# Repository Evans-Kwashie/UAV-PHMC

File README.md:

# UAV-PHMC
### Payload Health & Management Controller

UAV-PHMC is an embedded hardware project: a custom four-layer printed circuit board (PCB) for power management, health monitoring and payload interfacing on a small UAV.

The board is designed to be light and to run from a 2S battery pack. It was modelled around the Ornadyne O1, a crow-shaped, propeller-free flapping-wing reconnaissance drone. This is an independent design and is not affiliated with Ornadyne.

The repository contains the KiCad hardware design files, manufacturing outputs for PCB fabrication and assembly, and an early STM32 firmware foundation with host-side tests.

---

## Project Overview

The UAV-PHMC board is built around the **STM32G071KBUx** microcontroller. It regulates the battery input into the rails the airframe needs, monitors voltage and current, and gives a companion computer and a camera a protected supply and a serial link.

Key design areas include:

- Custom four-layer PCB design.
- STM32G071KBUx microcontroller integration.
- 2S battery input with polyfuse and TVS protection.
- Multi-rail power distribution with two buck regulators.
- Voltage and current monitoring.
- Companion connector and switched camera power connector.
- SWD debug through a Tag-Connect footprint.
- PCB fabrication and assembly preparation.

## Hardware Features

| Feature | Description |
|---|---|
| Microcontroller | STM32G071KBUx |
| PCB | Custom four-layer design |
| Battery input | 2S pack, with polyfuse (F1) and SMAJ10A TVS (D1) |
| Power regulation | Two TPS562202S buck converters |
| Current monitoring | INA226 with a 0.1 ohm shunt |
| Power rails | VBAT_RAW, VBAT_PROT, 5V, 5V_CAM, 3V3 |
| Communication | UART (USART2), I²C (I2C1) |
| Connectors | Battery (J1), companion (J3), camera power (J4) |
| Debug | SWD through Tag-Connect TC2030-NL |
| Design software | KiCad |

## Power Architecture

The hardware design incorporates multiple power domains to support the board and its connected peripherals.

| Power net | Purpose |
|---|---|
| VBAT_RAW | Raw battery input |
| VBAT_PROT | Battery rail after the input protection stage |
| 5V | Main regulated 5V supply |
| 5V_CAM | Camera power supply |
| 3V3 | Logic and microcontroller supply |

The design includes voltage and current monitoring using the INA226, supporting power-system observation and integration.

## Repository Structure

```text
UAV-PHMC/
│
├── hardware/
│   ├── bom/
│   │   └── hardware.csv
│   │
│   ├── gerbers/
│   │   ├── PHMC_gerbers.zip
│   │   ├── hardware-Front.gtl
│   │   ├── hardware-Back.gbl
│   │   ├── hardware-Edge_Cuts.gm1
│   │   └── ... fabrication layers and drill files
│   │
│   ├── libraries/          custom footprints and 3D models
│   ├── pick_place/
│   │   └── hardware-all.pos
│   │
│   ├── hardware.kicad_pro
│   ├── hardware.kicad_sch  top-level schematic
│   ├── Power_Input_Protection.kicad_sch
│   ├── Current_Sense.kicad_sch
│   ├── MCU.kicad_sch
│   ├── Connectors_Comms.kicad_sch
│   ├── hardware.kicad_pcb
│   ├── hardware.net
│   ├── hardware.glb
│   └── front.png, back.png, hardware.png
│
├── firmware/
│   ├── app/              portable application logic
│   ├── board/            board-specific signal definitions
│   ├── drivers/          portable drivers and conversions
│   ├── platform/stm32/   STM32 startup, entry point and linker script
│   ├── tests/            host-native unit tests
│   ├── third_party/      pinned CMSIS files and license notices
│   ├── CMakeLists.txt
│   ├── CMakePresets.json
│   └── README.md         firmware build, test and limitation details
│
├── references/             component datasheets
│   ├── stm32g071c8.pdf
│   ├── tps562202s.pdf
│   └── ina226.pdf
│
├── LICENSE
├── LICENSE-MIT
├── .gitignore
└── README.md
```

## Manufacturing Outputs

The repository includes the following manufacturing-related files:

**Bill of Materials (BOM)**
- `hardware/bom/hardware.csv`

**Gerber and Drill Files**
- `hardware/gerbers/`

**Pick-and-Place Data**
- `hardware/pick_place/hardware-all.pos`

**3D PCB Model**
- `hardware/hardware.glb`

**Gerber Archive**
- `hardware/gerbers/PHMC_gerbers.zip`

These files are provided to support PCB fabrication, component sourcing, assembly preparation, and design review.

Before manufacturing, verify that the Gerber outputs, drill files, BOM, and pick-and-place data correspond to the intended PCB revision.

## Opening the Hardware Design

1. Install [KiCad](https://www.kicad.org/).
2. Clone or download this repository.
3. Navigate to the `hardware/` directory.
4. Open `hardware.kicad_pro` in KiCad.
5. Inspect the schematic and PCB design as applicable.

The 3D model can also be inspected using a compatible 3D viewer.

## Programming and Boot

The board is programmed and debugged over SWD through the Tag-Connect TC2030-NL footprint (J2).

On the STM32G071, pin PA14 is shared between SWCLK and BOOT0. In this design the `SWCLK_BOOT0` net joins the Tag-Connect SWCLK pin, PA14 on U3, and a 10 kΩ pull-down resistor (R6) to ground.

- At reset the microcontroller samples BOOT0. With the pin low it boots the application from flash, and R6 holds the pin low by default.
- If the pin is held high at reset, for example by a debug probe driving SWCLK high, the microcontroller starts the STM32 system bootloader instead of the application.
- After startup PA14 operates as SWCLK.

If the board appears unresponsive with a probe attached, release the probe and reset the board again. The `nBOOT_SEL` option byte can be programmed so that the boot source comes from the option bytes instead of the pin. This frees PA14 from boot selection and removes pin-based bootloader entry.

## Firmware Development

The `firmware/` directory contains an early, buildable STM32G071 firmware skeleton:

- CMake and Ninja builds for STM32G071 using GNU Arm GCC.
- Pinned CMSIS startup and device support with third-party license notices.
- Fixed-point INA226 shunt-voltage and bus-voltage conversion.
- Portable camera-command state machine with host-side tests.
- ELF, BIN, HEX and linker-map build artifacts.

From `firmware/`, run the host tests:

```sh
cmake --preset host
cmake --build --preset host
ctest --preset host
```

Build for the STM32 target:

```sh
cmake --preset stm32-release
cmake --build --preset stm32-release
```

See [`firmware/README.md`](firmware/README.md) for prerequisites, artifact locations, dependency details and current limitations. Peripheral drivers, companion communication and physical camera-rail control are not yet implemented or validated.

### V1 camera-rail limitation

The camera regulator's active-high enable signal connects to PA12 [PA10], physical package pin 23. V1 has no external pull-down guaranteeing a disabled rail before firmware initializes the GPIO. Power-on and reset behavior is therefore unvalidated. The firmware uses `CAMERA_ON_COMMANDED` to distinguish a requested state from confirmed electrical behavior.

A future hardware revision should add an appropriately sized external pull-down and validate startup, reset and rail switching on the physical PCB.

## Project Status

**Hardware design, manufacturing outputs and initial firmware skeleton committed.**

The repository includes the PCB design, project configuration, BOM, Gerber fabrication files, drill data, pick-and-place coordinates, 3D model and early firmware source with host tests.

The inclusion of manufacturing outputs and firmware does not imply that the board has been fabricated, assembled, electrically validated, programmed, or flight-tested. Successful host tests and cross-compilation demonstrate software behavior and target buildability only.

## Tools & Technologies

- **KiCad**: PCB design and layout.
- **STM32**: Embedded microcontroller platform.
- **INA226**: Voltage and current monitoring.
- **TPS562202S**: Power regulation.
- **Gerber**: PCB fabrication data.
- **3D CAD**: PCB visualization and mechanical inspection.
- **C / CMSIS**: Portable firmware and STM32 device support.
- **CMake / Ninja / GNU Arm GCC**: Host and STM32 builds.
- **CTest**: Host-native unit testing.

## Licensing

### Hardware design

The hardware design files in this repository, including schematics, PCB layouts, manufacturing outputs and related hardware documentation, are licensed under the **CERN Open Hardware Licence Version 2 – Strongly Reciprocal (CERN-OHL-S-2.0)**. See [LICENSE](./LICENSE).

The complete source for this hardware design is available in this repository: https://github.com/Evans-Kwashie/UAV-PHMC

### Software

Any firmware, software or code in this repository that is explicitly identified as software is licensed under the **MIT License**. See [LICENSE-MIT](./LICENSE-MIT). Third-party components remain under their respective licences.

## Author

**Evans Klenam Kwashie-Seyram**

- GitHub: [@Evans-Kwashie](https://github.com/Evans-Kwashie)
- LinkedIn: [Evans Klenam Kwashie-Seyram](https://linkedin.com/in/evans-klenam-kwashie-seyram)
- Portfolio: [pcb-portfolio.vercel.app](https://pcb-portfolio.vercel.app)

---

*UAV-PHMC: custom embedded hardware for UAV systems.*

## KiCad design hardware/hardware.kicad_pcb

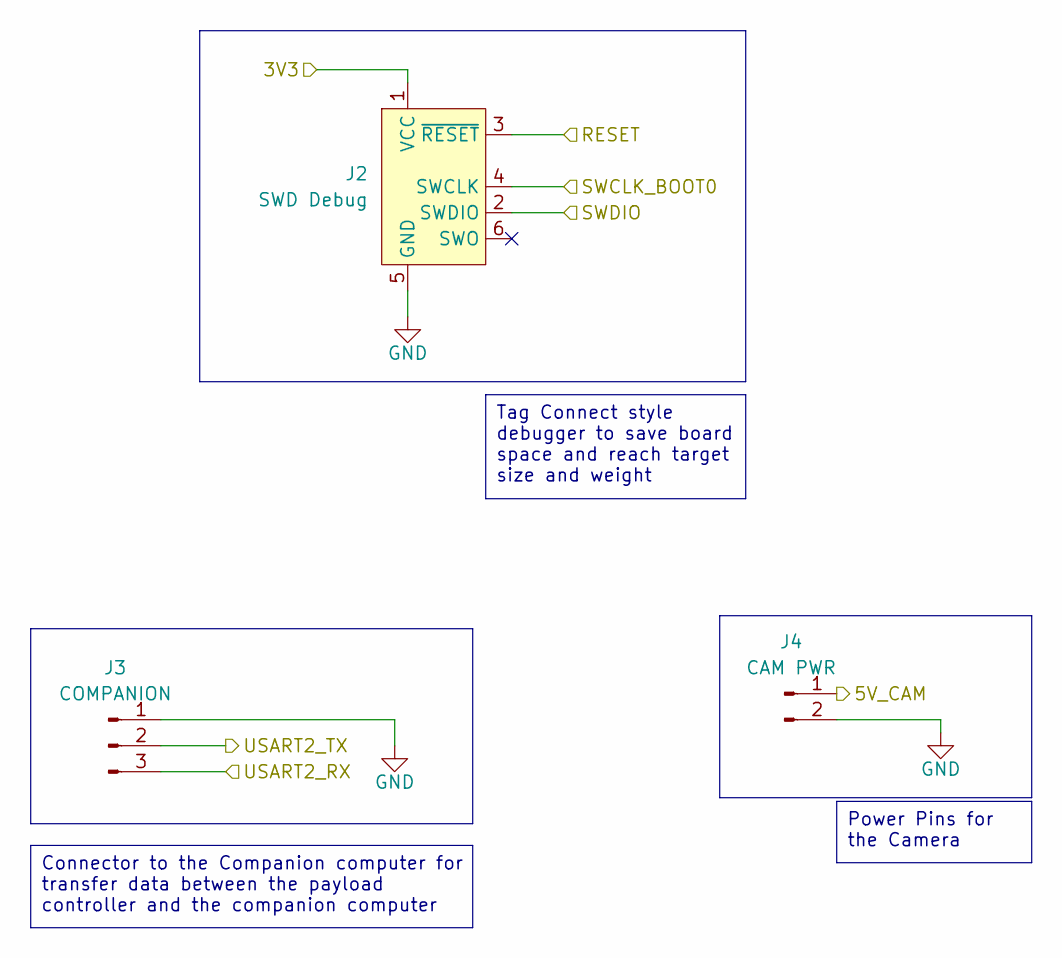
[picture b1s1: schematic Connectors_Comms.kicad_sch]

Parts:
J2: SWD Debug; Tag-Connect_TC2030-IDC-NL_2x03_P1.27mm_Vertical
J3: COMPANION; JST_SH_SM03B-SRSS-TB_1x03-1MP_P1.00mm_Horizontal
J4: CAM PWR; JST_SH_SM02B-SRSS-TB_1x02-1MP_P1.00mm_Horizontal

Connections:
/Connectors_Comms/3V3: J2.1 (VCC); also elsewhere on the board
/Connectors_Comms/5V_CAM: J4.1; also elsewhere on the board
/Connectors_Comms/RESET: J2.3 (~RESET); also elsewhere on the board
/Connectors_Comms/SWCLK_BOOT0: J2.4 (SWCLK); also elsewhere on the board
/Connectors_Comms/SWDIO: J2.2 (SWDIO); also elsewhere on the board
/Connectors_Comms/USART2_RX: J3.3; also elsewhere on the board
/Connectors_Comms/USART2_TX: J3.2; also elsewhere on the board
GND: J2.5 (GND), J3.1, J4.2; also elsewhere on the board

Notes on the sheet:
Tag Connect style debugger to save board space and reach target size and weight
Power Pins for the Camera
Connector to the Companion computer for transfer data between the payload controller and the companion computer

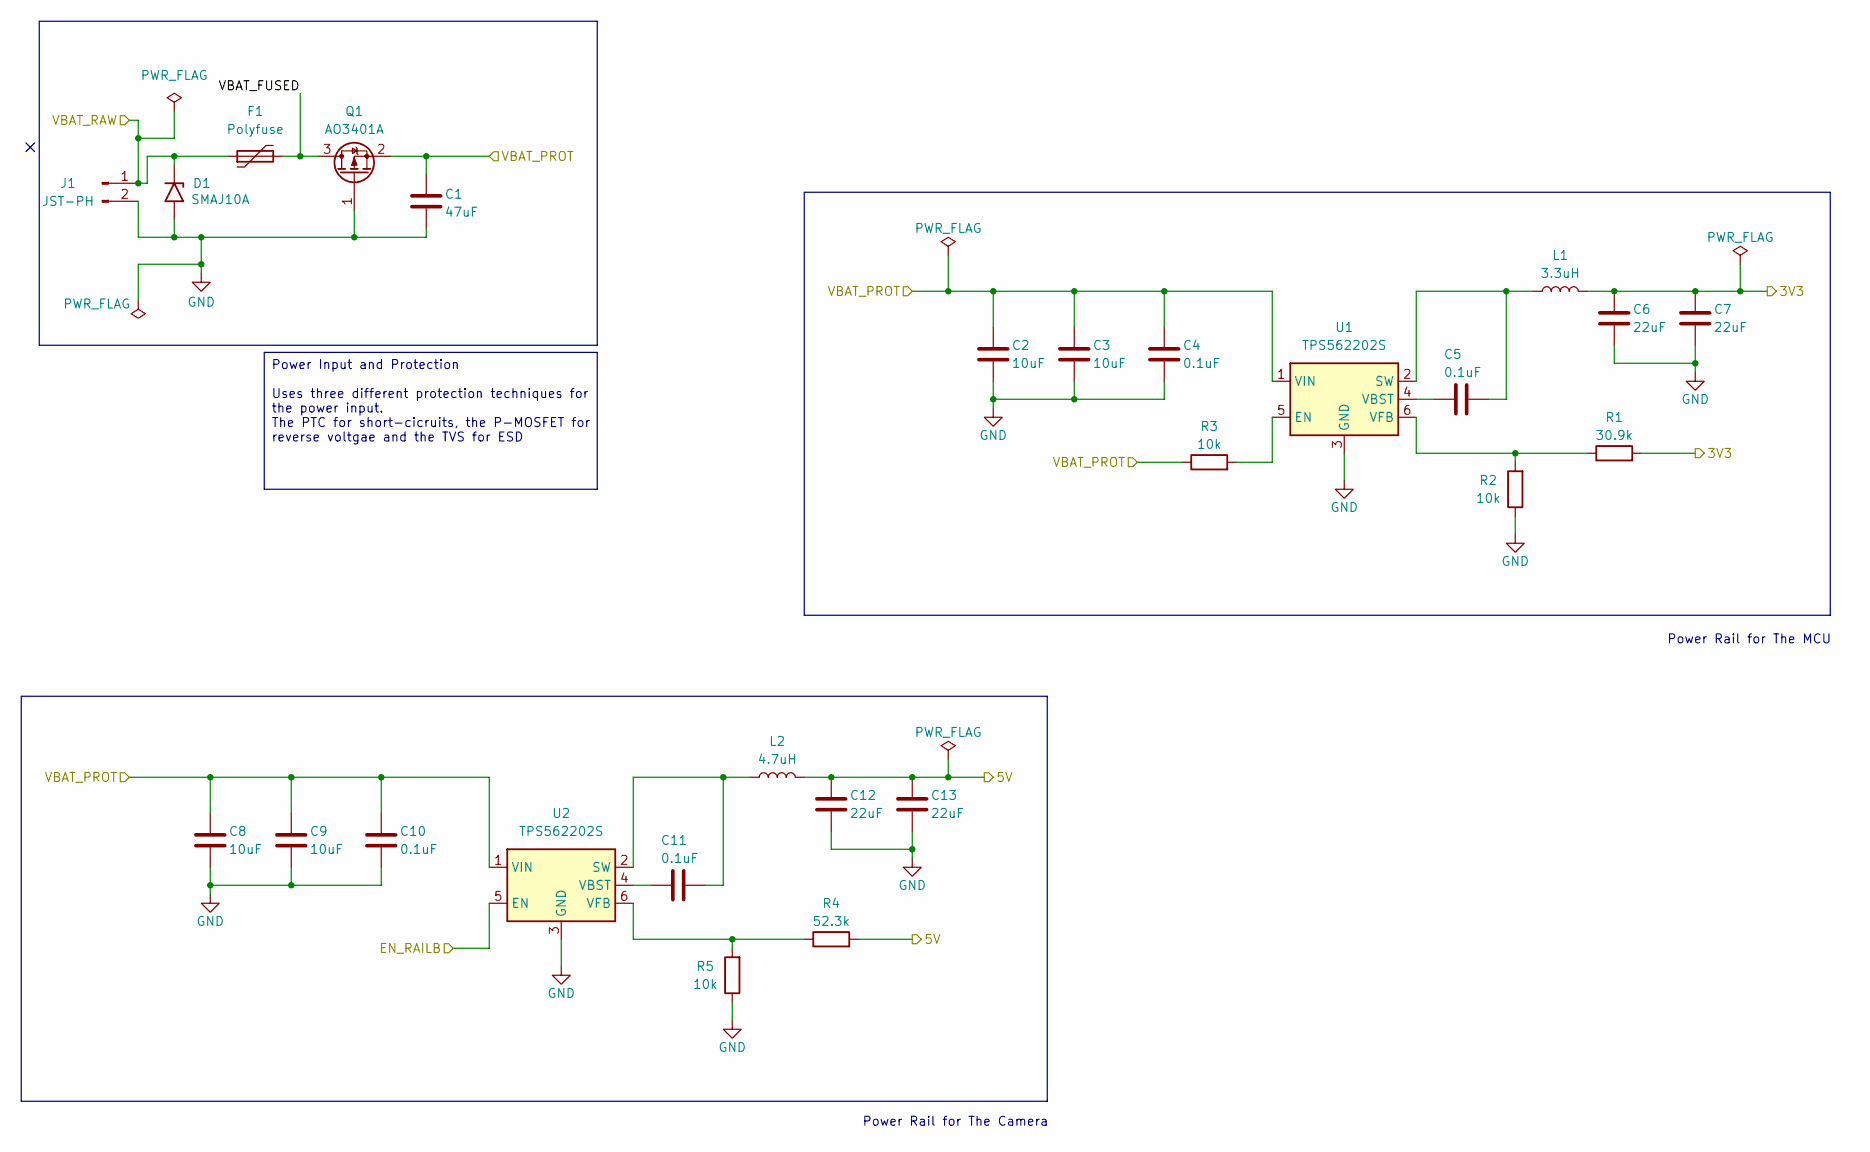
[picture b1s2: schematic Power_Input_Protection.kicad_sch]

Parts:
C1: 47uF; C_1210_3225Metric
C2, C3, C8, C9: 10uF; C_0805_2012Metric
C4, C5, C10, C11: 0.1uF; C_0603_1608Metric
C6, C7, C12, C13: 22uF; C_1206_3216Metric
D1: SMAJ10A; D_SMA
F1: Polyfuse; F_1812_4532Metric
J1: JST-PH; JST_PH_S2B-PH-SM4-TB_1x02-1MP_P2.00mm_Horizontal
L1: 3.3uH; L_Coilcraft_XFL2010
L2: 4.7uH; L_Coilcraft_XAL4020-XXX
Q1: AO3401A; SOT-23
R1: 30.9k; R_0201_0603Metric
R2, R3, R5: 10k; R_0201_0603Metric
R4: 52.3k; R_0201_0603Metric
U1, U2: TPS562202S; SOT-563

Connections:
/Connectors_Comms/3V3: C6.1, C7.1, L1.2, R1.2; also elsewhere on the board
/Current_Sense/5V: C12.1, C13.1, L2.2, R4.2; also elsewhere on the board
/Current_Sense/VBAT_PROT: C1.1, C2.1, C3.1, C4.1, C8.1, C9.1, C10.1, Q1.2 (S), R3.1, U1.1 (VIN), U2.1 (VIN); also elsewhere on the board
/Current_Sense/VBAT_RAW: D1.1 (A1), F1.1, J1.1; also elsewhere on the board
/MCU/EN_RAILB: U2.5 (EN); also elsewhere on the board
/Power_Input_Protection/VBAT_FUSED: F1.2, Q1.3 (D)
GND: C1.2, C2.2, C3.2, C4.2, C6.2, C7.2, C8.2, C9.2, C10.2, C12.2, C13.2, D1.2 (A2), J1.2, Q1.1 (G), R2.1, R5.1, U1.3 (GND), U2.3 (GND); also elsewhere on the board
unnamed: R3.2, U1.5 (EN)
unnamed: C5.2, L1.1, U1.2 (SW)
unnamed: C5.1, U1.4 (VBST)
unnamed: R1.1, R2.2, U1.6 (VFB)
unnamed: C11.2, L2.1, U2.2 (SW)
unnamed: C11.1, U2.4 (VBST)
unnamed: R4.1, R5.2, U2.6 (VFB)

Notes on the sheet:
Power Rail for The Camera
Power Rail for The MCU
Power Input and Protection Uses three different protection techniques for the power input. The PTC for short-cicruits, the P-MOSFET for reverse voltgae and the TVS for ESD

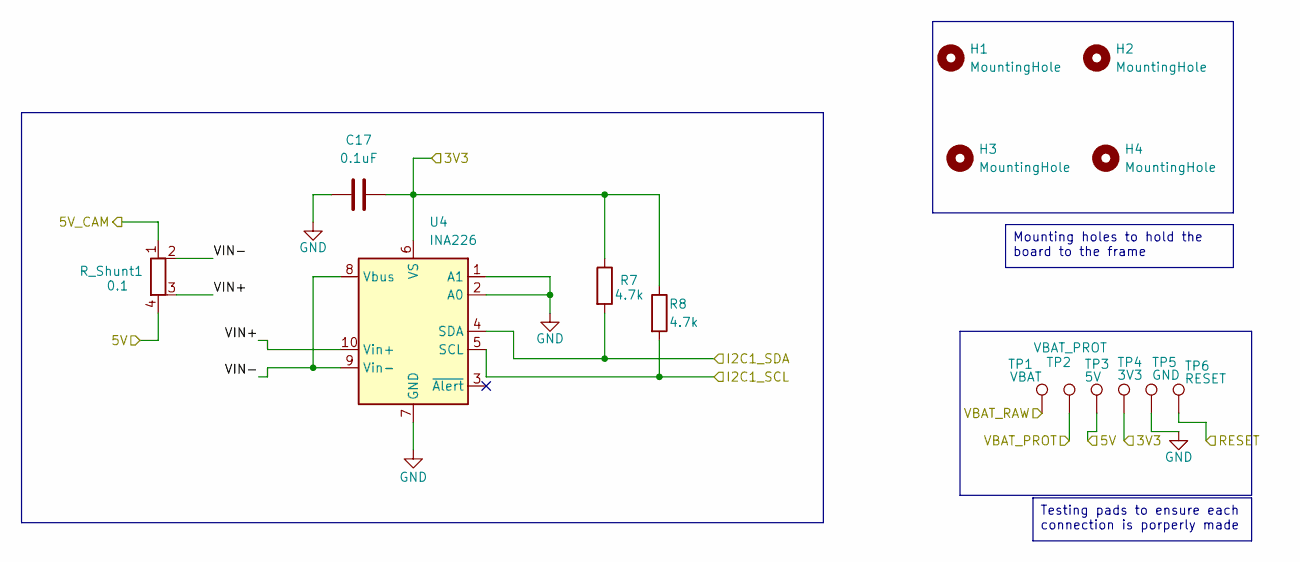
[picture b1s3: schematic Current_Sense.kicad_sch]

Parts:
C17: 0.1uF; C_0603_1608Metric
H1, H2, H3, H4: MountingHole; MountingHole_2.2mm_M2
R7, R8: 4.7k; R_0201_0603Metric
R_Shunt1: 0.1; R_Shunt_Vishay_WSK2512_6332Metric_T2.21mm
TP1: VBAT; TestPoint_Pad_D1.0mm
TP2: VBAT_PROT; TestPoint_Pad_D1.0mm
TP3: 5V; TestPoint_Pad_D1.0mm
TP4: 3V3; TestPoint_Pad_D1.0mm
TP5: GND; TestPoint_Pad_D1.0mm
TP6: RESET; TestPoint_Pad_D1.0mm
U4: INA226; TSSOP-10_3x3mm_P0.5mm

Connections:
/Connectors_Comms/3V3: C17.2, R7.1, R8.1, TP4.1 (1_1), U4.6 (VS); also elsewhere on the board
/Connectors_Comms/5V_CAM: R_Shunt1.1; also elsewhere on the board
/Connectors_Comms/RESET: TP6.1 (1_1); also elsewhere on the board
/Current_Sense/5V: R_Shunt1.4, TP3.1 (1_1); also elsewhere on the board
/Current_Sense/I2C1_SCL: R8.2, U4.5 (SCL); also elsewhere on the board
/Current_Sense/I2C1_SDA: R7.2, U4.4 (SDA); also elsewhere on the board
/Current_Sense/VBAT_PROT: TP2.1 (1_1); also elsewhere on the board
/Current_Sense/VBAT_RAW: TP1.1 (1_1); also elsewhere on the board
/Current_Sense/VIN+: R_Shunt1.3, U4.10 (Vin+)
/Current_Sense/VIN-: R_Shunt1.2, U4.8 (Vbus), U4.9 (Vin-)
GND: C17.1, TP5.1 (1_1), U4.1 (A1), U4.2 (A0), U4.7 (GND); also elsewhere on the board

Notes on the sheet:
Testing pads to ensure each connection is porperly made
Mounting holes to hold the board to the frame

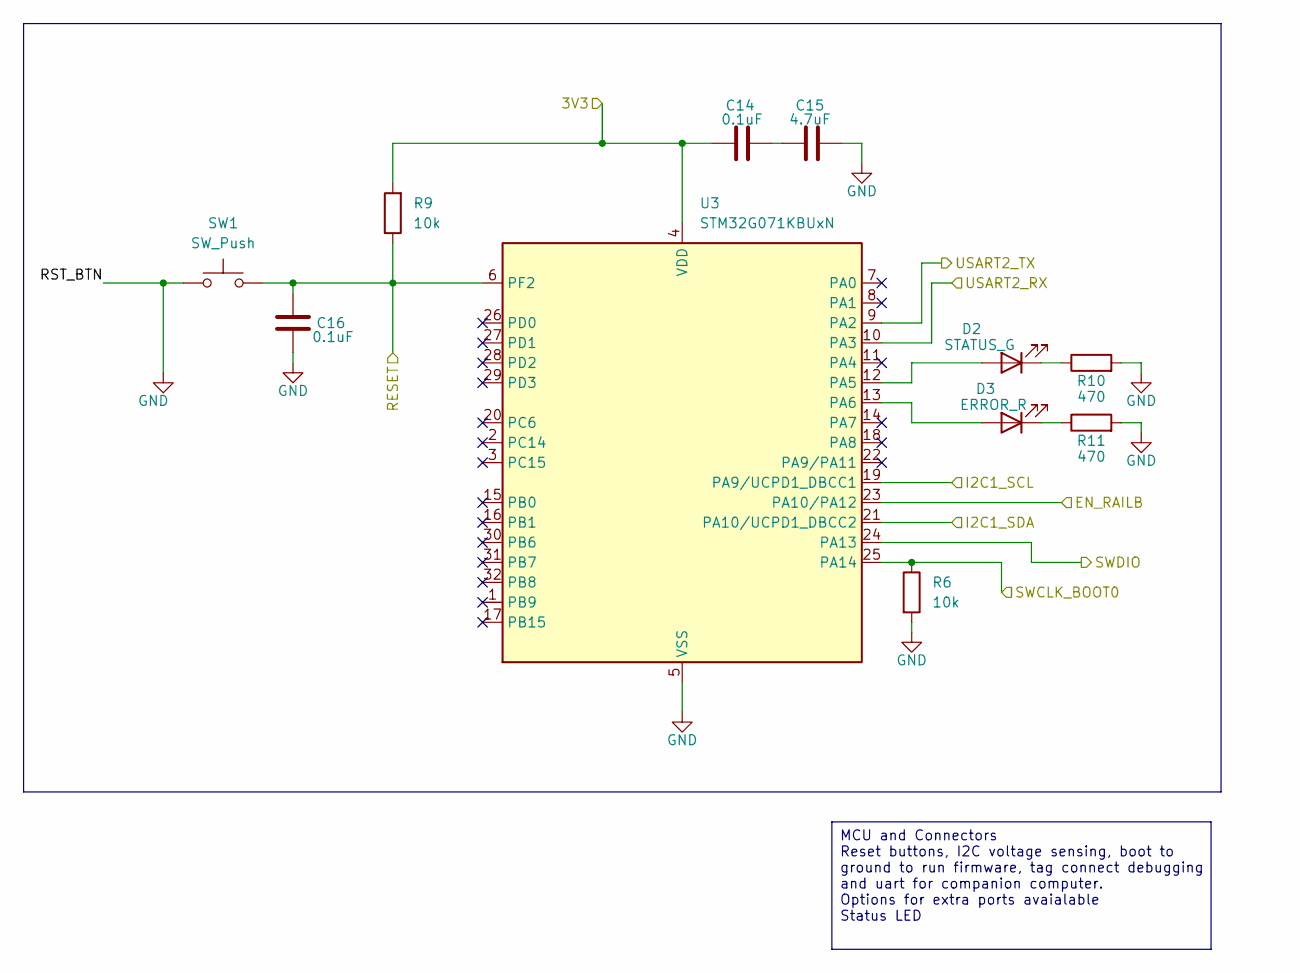
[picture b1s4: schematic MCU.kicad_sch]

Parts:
C14, C16: 0.1uF; C_0603_1608Metric
C15: 4.7uF; C_0603_1608Metric
D2: STATUS_G; LED_0201_0603Metric
D3: ERROR_R; LED_0201_0603Metric
R6, R9: 10k; R_0201_0603Metric
R10, R11: 470; R_0201_0603Metric
SW1: SW_Push; SW_SPST_EVQP2_MiddlePushTravel_H2.5mm
U3: STM32G071KBUxN; QFN-32-1EP_5x5mm_P0.5mm_EP3.45x3.45mm

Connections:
/Connectors_Comms/3V3: C14.1, R9.2, U3.4 (VDD); also elsewhere on the board
/Connectors_Comms/RESET: C16.1, R9.1, SW1.2, U3.6 (PF2); also elsewhere on the board
/Connectors_Comms/SWCLK_BOOT0: R6.1, U3.25 (PA14); also elsewhere on the board
/Connectors_Comms/SWDIO: U3.24 (PA13); also elsewhere on the board
/Connectors_Comms/USART2_RX: U3.10 (PA3); also elsewhere on the board
/Connectors_Comms/USART2_TX: U3.9 (PA2); also elsewhere on the board
/Current_Sense/I2C1_SCL: U3.19 (PA9/UCPD1_DBCC1); also elsewhere on the board
/Current_Sense/I2C1_SDA: U3.21 (PA10/UCPD1_DBCC2); also elsewhere on the board
/MCU/EN_RAILB: U3.23 (PA10/PA12); also elsewhere on the board
GND: C15.2, C16.2, R6.2, R10.2, R11.2, SW1.1, U3.5 (VSS), U3.33 (VSS); also elsewhere on the board
unnamed: C14.2, C15.1
unnamed: D2.2 (A), U3.12 (PA5)
unnamed: D2.1 (K), R10.1
unnamed: D3.2 (A), U3.13 (PA6)
unnamed: D3.1 (K), R11.1

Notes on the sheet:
MCU and Connectors Reset buttons, I2C voltage sensing, boot to ground to run firmware, tag connect debugging and uart for companion computer. Options for extra ports avaialable Status LED

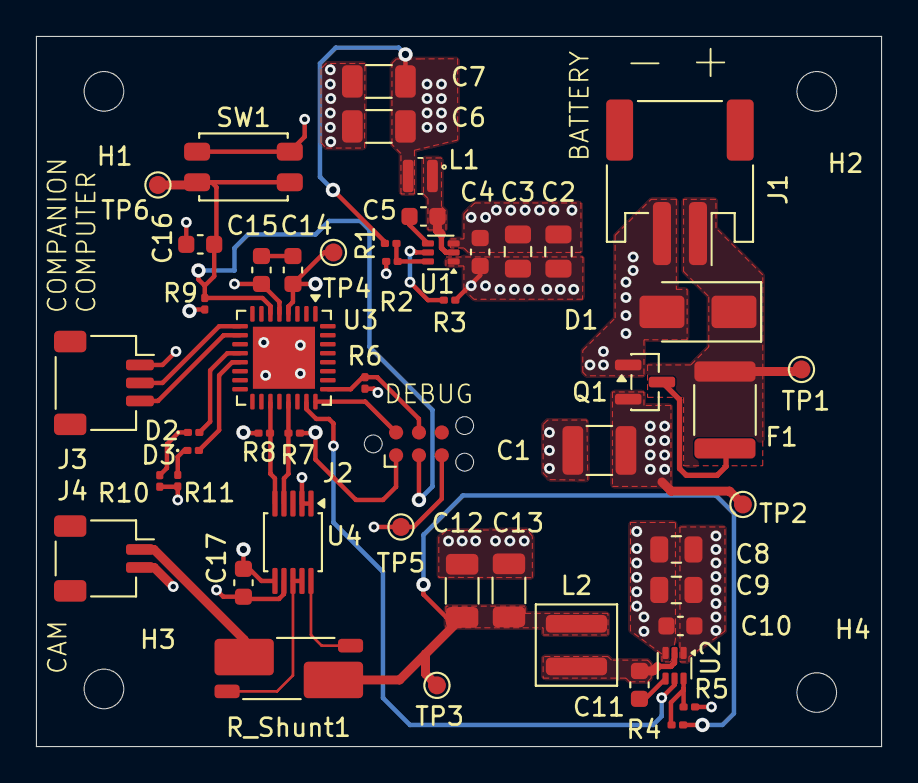
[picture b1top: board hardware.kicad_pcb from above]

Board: 4 copper layers, 46.9 x 39.5 mm, 55 parts (0 on the bottom side), 29 nets.
